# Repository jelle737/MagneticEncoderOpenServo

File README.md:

# MagneticEncoderOpenServo
A programmable servo capable of turning a defined 1 turn 360° (or more)

Video on youtube:

* A programmable servo, based on ATMEGA328P, TLE5012B, MC34931 or DRV8837, using the arduino enviroment
* It's a defined travel servo, capable of going beyond the limits that a potentiometer has, without adding extra gears. It uses a magnet encoder to read it's position instead of a potentiometer.

More information and images are to be found [on this rc groups thread](https://www.rcgroups.com/forums/showthread.php?3154439-1-turn-360%C2%B0-servo "1 turn 360° servo").

## Software

The software programmed as is has a travel of 376° between the control pulses of 1000µs and 2000µs. The pulses can be wider but *as is* it is limited between around 800µs and 2200µs. providing a travel of more then 450°.

The software can be reprogrammed to do the following:
* Become a continious rotating servo.
* Be a multiple turn servo, like a 10 turn sail winch servo.
* Be current limited, the hardware is capable but not software implemented.
* Have a speed limited movement.
* Be a digital classic servo with a travel of just 90° or 180°.
* Be programmed as time lapse very slow turning servo since there are 2^15 steps of precision.
* Be programmed to accept commands instead of a PWM signal, or have different interaction interfaces.

Dificulty of implementing varies on the topic.

Possible drawbacks:
* Since it uses a magnet, it might be interfered with by an external magnet.
* If the shaft is turned >180° degrees while unpowered the servo will skip a turn, it should not be turned >90° when powered down to prevent for this unwanted behaviour.
* Since there is no endstop there is a software implementation to catch where in a turn it was depowered. This uses EEPROM which has a 100000 write cycle. In my software implementation every 1/8th of a circle the position is saved. This is done in a ring memory containing 256 bytes and requires the old value to be erased (written with 0) and the next position to be written with the new position value. This means technically after 1600000 turns the atmega chips EEPROM might stop working correctly. If you succeed in breaking the EEPROM there are software solutions to prolong the atmega328p's life.

Possible improvements:
* In a fast movement the servo has a tendency to overshoot it's target value. At this moment a P&D is implemented in the PID, but I feel like the I could help out to not overshoot the target and have a more gracefull reach to the target value.
* Code could be improved to integrated safety features like current limiting.
* Code could be cleaned up.

## Hardware

The required parts next the pcb's and it's components are:
* A donor servo for it's housing, gears, motor and shaft of the potentiometer.
* A Diametrically Magnetised round magnet, hard to find can possibly be substitued by a cube magnet.
* Basic components of the hardware pcb are: ATMEGA328P, TLE5012B, MC34931 or DRV8837

## Open Source

This fork is software that is **open source** and is available free of charge without warranty to all users.

The license is GPL3.

## Project/Fork History

Based on OpenServo: https://github.com/ginge/OpenServo

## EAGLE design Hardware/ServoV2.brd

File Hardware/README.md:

# MagneticEncoderOpenServo
A programmable servo capable of turning a defined 1 turn 360° (or more)

## Servo Board & Schematic

First version to fit in a regular sized servo like Tower Pro MG995.

## ServoV2 Board & Schematic

Second slimed down version to fit a micro sized servo like EMAX ES08MA.

## Open Source

This fork is software that is **open source** and is available free of charge without warranty to all users.

The license is GPL3.

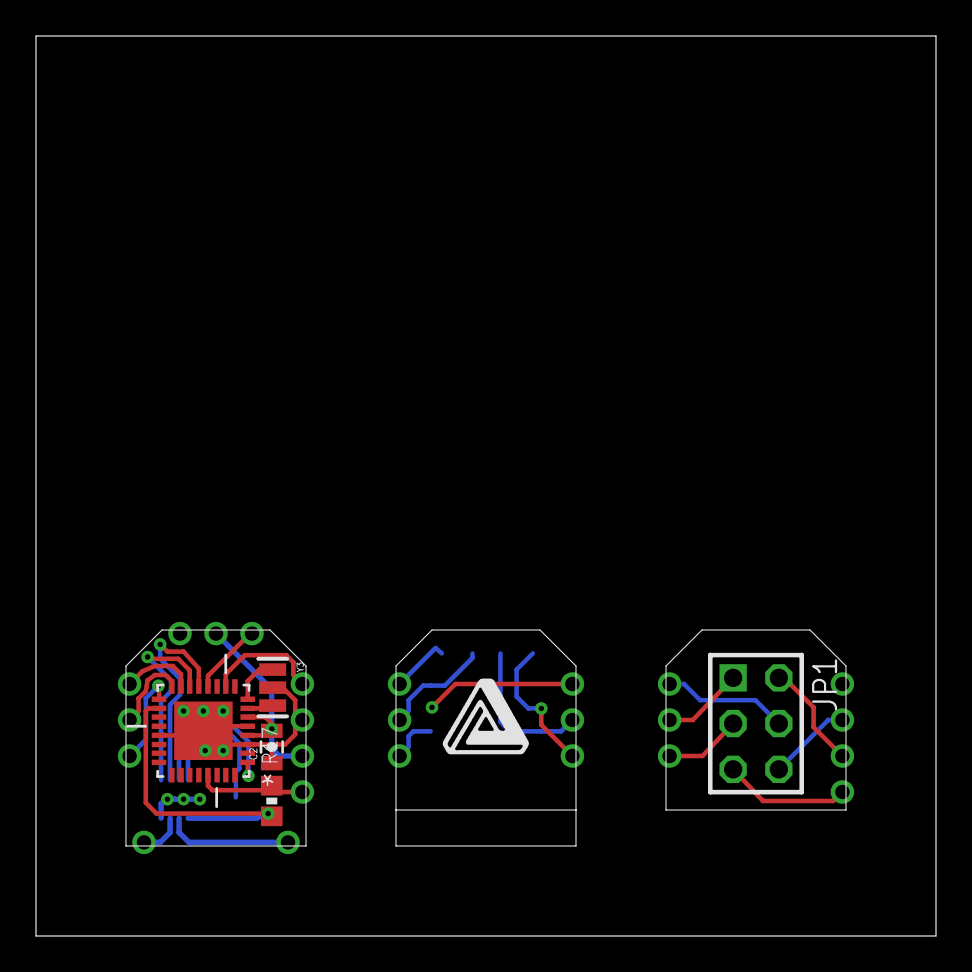
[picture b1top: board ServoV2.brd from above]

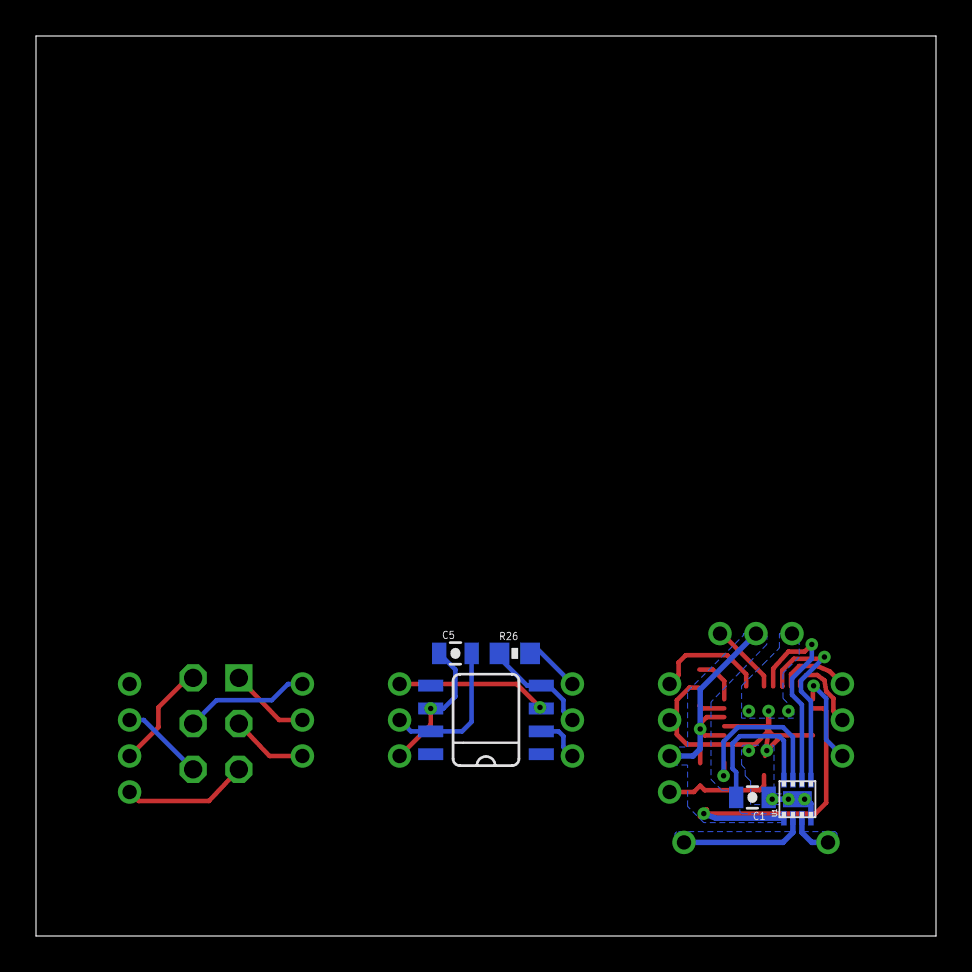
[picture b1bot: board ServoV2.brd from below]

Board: 2 copper layers, 50.0 x 50.0 mm, 13 parts (5 on the bottom side), 27 nets.

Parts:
C1, C2, C5: 100nF; 0805-CAP
IC4: TLE5012B E1000X; SO08
JP1: 2X03
R17: 1k; 0603
R26: 4.7k; 0603
U1: DRV8837; DSG
U2: ATMEGA328P-MU; QFN50P500X500X100-33N
U$1: 2TOPSIG
U$2: 2BOTSIG; 2BOTTOMSIG
U$3: PRGRMR
Y3: 16MHz; RESONATOR

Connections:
D3~: U1.7, U2.1
D6~: U2.10, U$2.P$7
D8: U2.12, U$2.P$3
D9~: U1.6, U2.13
D10/SS: U1.5, U2.14
D11~/MOSI: U2.15, U$2.P$4
D12/MISO: U2.16, U$2.P$5
D13/SCK: U2.17, U$2.P$6
GND: C1.1, C2.1, U1.4, U1.PAD, U2.3, U2.5, U2.21, U2.33, U$2.P$1, U$2.P$8, Y3.2
MISO: IC4.4, R26.1, U$1.P$5
MOSI: R26.2, U$1.P$4
OUT1: U1.2, U$2.P$11
OUT2: U1.3, U$2.P$10
PGND: JP1.6, U$3.P$8
PMISO: JP1.1, U$3.P$5
PMOSI: JP1.4, U$3.P$4
PRST: JP1.5, U$3.P$1
PSCL: JP1.3, U$3.P$6
PVCC: JP1.2, U$3.P$9
RESET: R17.2, U2.29, U$2.P$12
SCK: IC4.2, U$1.P$6
SS: IC4.3, U$1.P$7
TGND: C5.2, IC4.7, U$1.P$8
TVCC: C5.1, IC4.6, U$1.P$9
VCC: C1.2, C2.2, R17.1, U1.1, U1.8, U2.4, U2.6, U2.18, U$2.P$2, U$2.P$9
XTAL1: U2.7, Y3.3
XTAL2: U2.8, Y3.1

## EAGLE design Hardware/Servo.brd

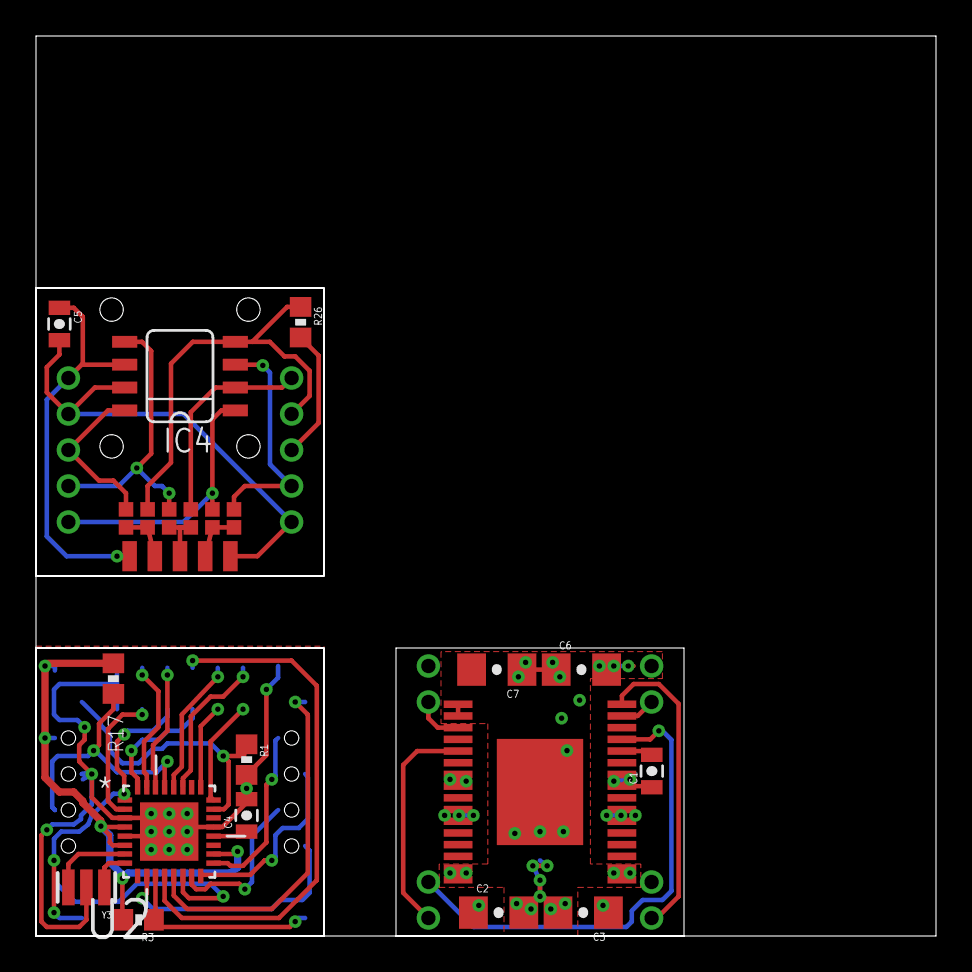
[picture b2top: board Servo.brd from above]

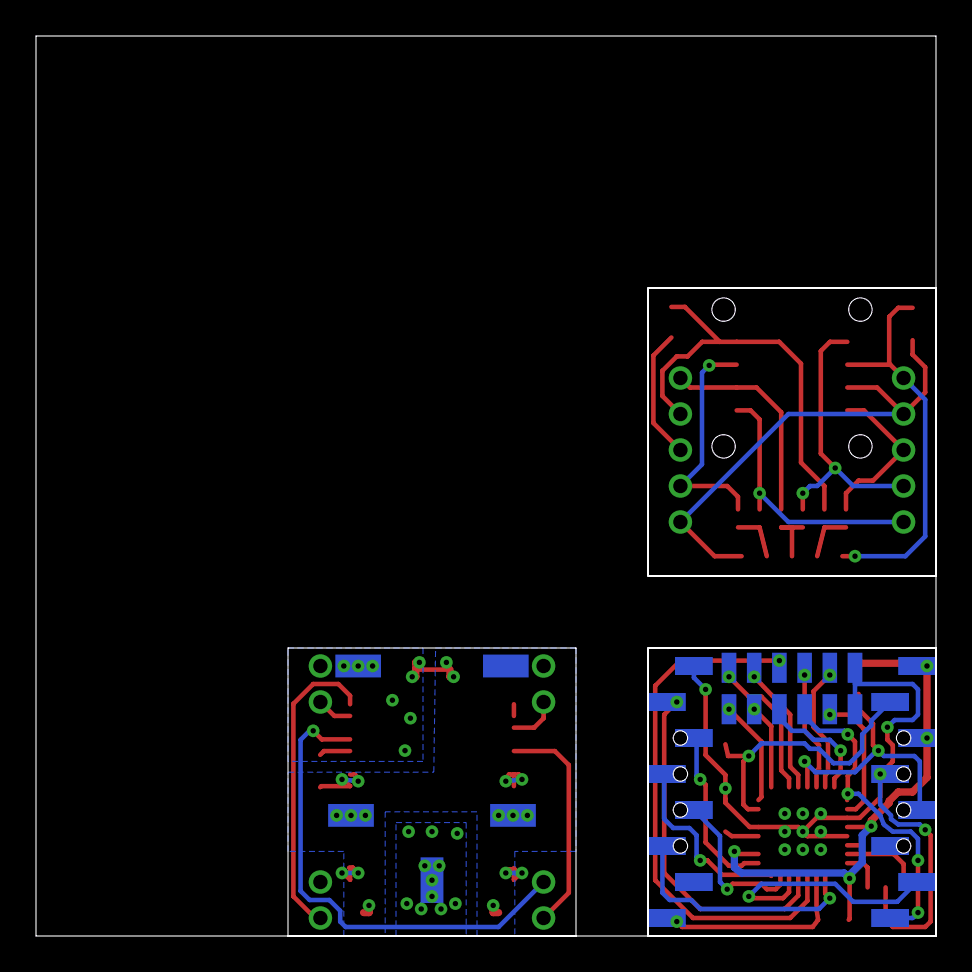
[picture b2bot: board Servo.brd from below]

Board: 2 copper layers, 50.0 x 50.0 mm, 25 parts (6 on the bottom side), 46 nets.

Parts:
C1: 30-100nF; 0805-CAP
C2, C3, C6, C7: 1.0uF; 1206-CAP
C4: 0.33uF; 0805-CAP
C5: 100nF; 0805-CAP
IC4: TLE5012B E1000X; SO08
R1: 430; 0603
R3: 2k; 0603
R17: 1k; 0603
R26: 4.7k; 0603
U2: ATMEGA328P-MU; QFN50P500X500X100-33N
U$1: MIDDLE; MIDDLE2
U$2: TOP
U$3: BOTTOM
U$4: MC34931EK
U$5, U$6, U$7, U$8, U$14: PAD
U$10: MIDDLE3
U$13: TOP2
Y3: 16MHz; RESONATOR

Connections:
A0: R1.1, U2.23, U$1.7
A1: U2.24, U$10.7
A2: U2.25, U$10.8
A4: U2.27, U$10.1
A5: U2.28, U$10.2
AREF: C4.1, U2.20
BGND: C2.2, C3.2, C6.2, C7.2, U$3.8, U$4.P$1, U$4.P$2, U$4.P$15, U$4.P$16, U$4.P$17, U$4.P$18, U$4.P$33, U$7.P$1, U$14.P$1
D0/RX: U2.30, U$10.4
D1/TX: U2.31, U$10.5
D2: U2.32, U$10.9
D3~: U2.1, U$1.1, U$10.10
D4: U2.2, U$10.11
D6~: U2.10, U$1.11
D7: R3.1, U2.11, U$1.9
D8: U2.12, U$10.3
D9~: U2.13, U$1.15
D10/SS: U2.14, U$1.2
D11~/MOSI: U2.15, U$1.12
D12/MISO: U2.16, U$1.13
D13/SCK: U2.17, U$1.14
EN: U$3.1, U$4.P$5
FAULT: U$3.5, U$4.P$32
FB: U$3.3, U$4.P$3
IFA: IC4.5, U$2.2, U$13.13
IFB: IC4.8, U$2.3, U$13.11
IFC: IC4.1, U$2.1, U$13.15
MGND: C4.2, R1.2, U2.3, U2.5, U2.21, U2.33, U$1.5, U$1.16, U$10.6, U$10.12, Y3.2
MISO: IC4.4, R26.1, U$2.9, U$13.12
MOSI: R26.2, U$2.8
MVCC: R3.2, R17.1, U2.4, U2.6, U2.18, U$1.6, U$1.8
unnamed: U$13.21, U$13.22, U$13.32
unnamed: U$13.23, U$13.24, U$13.33
unnamed: U$13.25, U$13.26, U$13.34
unnamed: C1.2, U$4.P$28
OUT1: U$4.P$10, U$4.P$11, U$6.P$1
OUT2: U$4.P$22, U$4.P$23, U$5.P$1
PWM1: U$3.7, U$4.P$31
PWM2: U$3.2, U$4.P$29
RESET: R17.2, U2.29, U$1.4
SCK: IC4.2, U$2.10, U$13.14
SS: IC4.3, U$2.7, U$13.16
TGND: C5.2, IC4.7, U$2.4, U$2.6, U$13.35
TVCC: C5.1, IC4.6, U$2.5, U$13.31
VIN: C1.1, C2.1, C3.1, C6.1, C7.1, U$3.4, U$4.P$7, U$4.P$8, U$4.P$25, U$4.P$26, U$8.P$1
XTAL1: U2.7, Y3.3
XTAL2: U2.8, Y3.1

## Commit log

2018-09-04 Explaining what this Git will be about, initial commit.
2018-09-09 Rename Repository
2018-11-03 Initial release project upload.
2018-11-15 Multiple turn information and what to know and how to implement safely.
2019-01-19 Mayor update, full PID controller, timeout timer fixed, full code cleanup, local and global variables instead of variable table.
2019-03-03 Create and catch crc errors on angle measurements correctly. Add video and forum links.
2019-06-24 Fix spi timing to represent minium timings as in the datasheet of TLE5012B
2019-12-24 Custom bootloader to allow for programming over the servo wire. 1-wire bootloader.
2019-12-24 Code for the dedicated programmer to work with the custom bootloader to allow for upload code over the servo plug. 1-wire programmer.
2019-12-24 Schematic and board design for the micro servo design of this project. Merry Christmas.

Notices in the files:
parts and their libraries:
SparkFun-Resistors: Licensing: Creative Commons ShareAlike 4.0 International - https://creativecommons.org/licenses/by-sa/4.0
